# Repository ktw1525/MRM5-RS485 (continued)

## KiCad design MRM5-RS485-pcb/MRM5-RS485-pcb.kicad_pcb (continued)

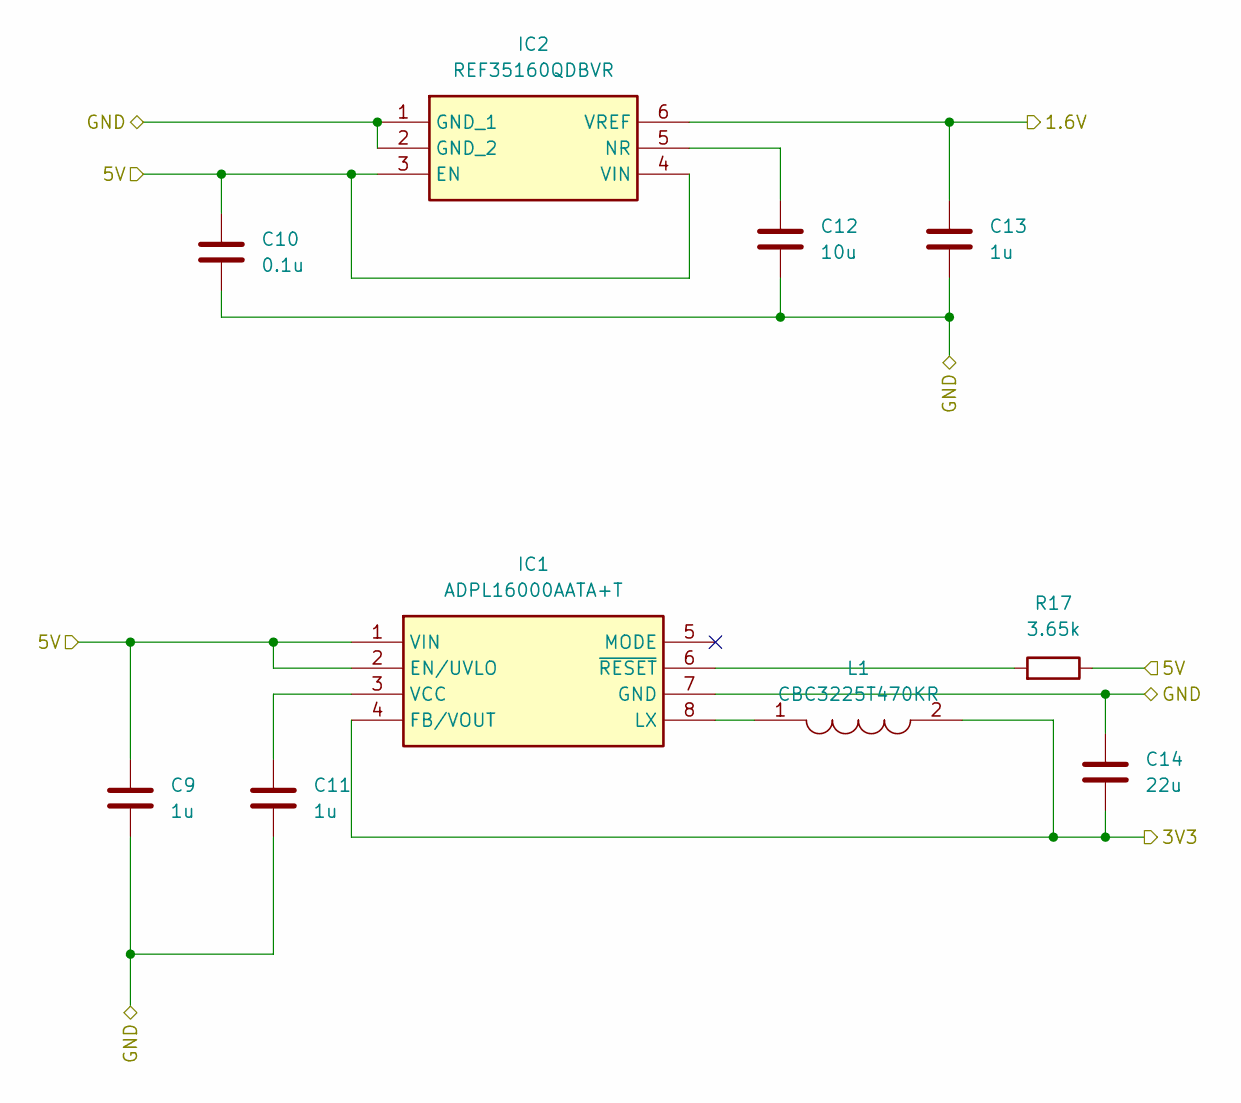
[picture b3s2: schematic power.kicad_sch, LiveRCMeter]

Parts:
C9, C11, C13: 1u; C_0402_1005Metric
C10: 0.1u; C_0402_1005Metric
C12: 10u; C_0805_2012Metric_Pad1.15x1.40mm
C14: 22u; C_0805_2012Metric_Pad1.15x1.40mm
IC1: ADPL16000AATA+T; ADPL16000AATAT; Manufacturer_Part_Number ADPL16000AATA+T; Mouser Part Number 700-ADPL16000AATA+T
IC2: REF35160QDBVR; SOT95P280X145-6N; Manufacturer_Part_Number REF35160QDBVR; Mouser Part Number 595-REF35160QDBVR
L1: CBC3225T470KR; INDC3225X270N; Manufacturer_Part_Number CBC3225T470KR; Mouser Part Number 963-CBC3225T470KR
R17: 3.65k; R_0402_1005Metric

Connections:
+1V6: C13.2, IC2.6 (VREF); also elsewhere on the board
+3V3: C14.1, IC1.4 (FB/VOUT), L1.2; also elsewhere on the board
+5V: C9.2, C10.2, IC1.1 (VIN), IC1.2 (EN/UVLO), IC2.3 (EN), IC2.4 (VIN), R17.2; also elsewhere on the board
GND: C9.1, C10.1, C11.1, C12.1, C13.1, C14.2, IC1.7 (GND), IC2.1 (GND_1), IC2.2 (GND_2); also elsewhere on the board
unnamed: IC1.8 (LX), L1.1
unnamed: C11.2, IC1.3 (VCC)
unnamed: IC1.6 (~RESET), R17.1
unnamed: C12.2, IC2.5 (NR)

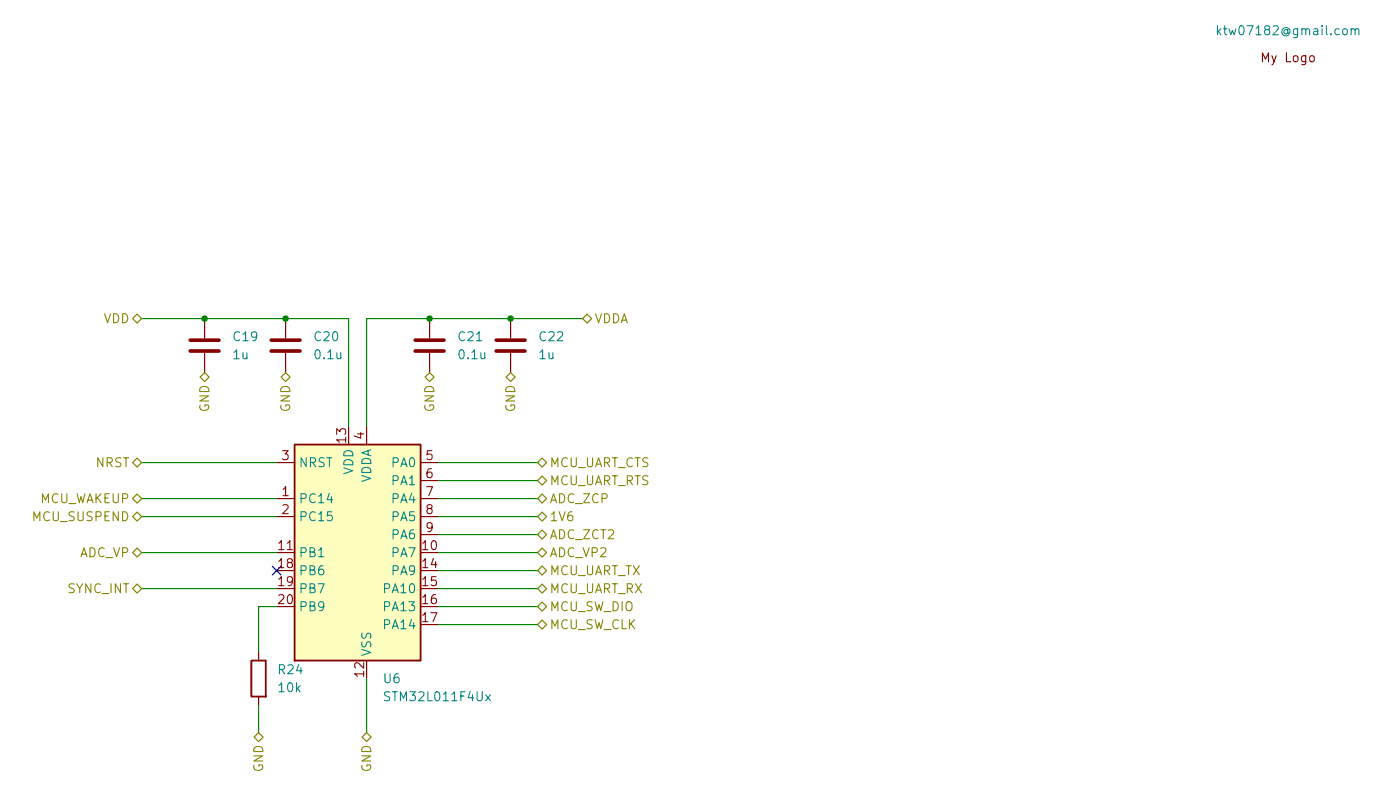
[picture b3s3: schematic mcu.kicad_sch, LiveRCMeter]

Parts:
C19, C22: 1u; C_0402_1005Metric
C20, C21: 0.1u; C_0402_1005Metric
R24: 10k; R_0402_1005Metric
Symbol1: ktw07182@gmail.com; ktw07182_logo
U6: STM32L011F4Ux; ST_UFQFPN-20_3x3mm_P0.5mm

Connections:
+1V6: U6.8 (PA5); also elsewhere on the board
+3V3: C19.2, C20.2, C21.2, C22.2, U6.4 (VDDA), U6.13 (VDD); also elsewhere on the board
/Analog/sigV: U6.11 (PB1); also elsewhere on the board
/Analog/sigV2: U6.10 (PA7); also elsewhere on the board
/Analog/sigZ: U6.7 (PA4); also elsewhere on the board
/Analog/sigZ2: U6.9 (PA6); also elsewhere on the board
/F1: U6.2 (PC15); also elsewhere on the board
/F2: U6.1 (PC14); also elsewhere on the board
/F3: U6.15 (PA10); also elsewhere on the board
/F4: U6.14 (PA9); also elsewhere on the board
/F5: U6.5 (PA0); also elsewhere on the board
/F6: U6.6 (PA1); also elsewhere on the board
/Interface/SYNC: U6.19 (PB7); also elsewhere on the board
/SW1: U6.3 (NRST); also elsewhere on the board
/SW2: U6.17 (PA14); also elsewhere on the board
/SW3: U6.16 (PA13); also elsewhere on the board
GND: C19.1, C20.1, C21.1, C22.1, R24.1, U6.12 (VSS); also elsewhere on the board
unnamed: R24.2, U6.20 (PB9)

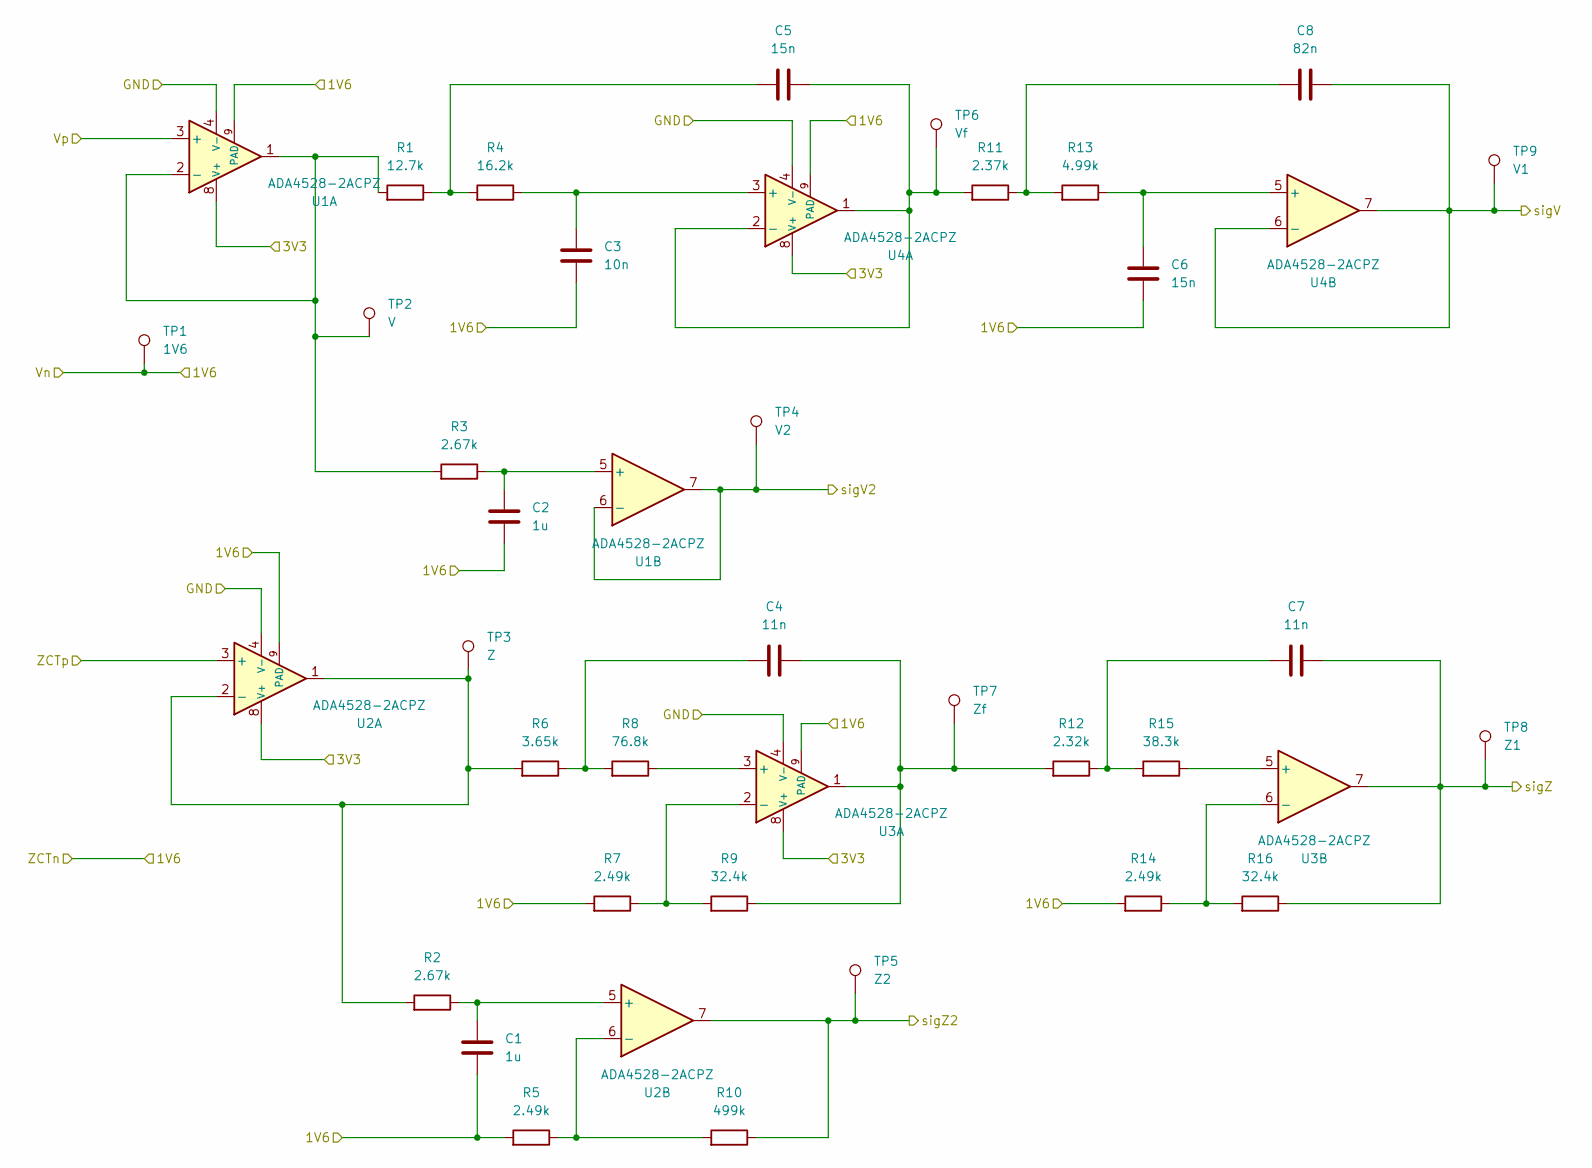
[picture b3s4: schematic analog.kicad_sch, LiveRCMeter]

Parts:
C1, C2: 1u; C_0402_1005Metric
C3: 10n; C_0402_1005Metric
C4, C7: 11n; C_0402_1005Metric
C5, C6: 15n; C_0402_1005Metric
C8: 82n; C_0402_1005Metric
R1: 12.7k; R_0402_1005Metric
R2, R3: 2.67k; R_0402_1005Metric
R4: 16.2k; R_0402_1005Metric
R5, R7, R14: 2.49k; R_0402_1005Metric
R6: 3.65k; R_0402_1005Metric
R8: 76.8k; R_0402_1005Metric
R9, R16: 32.4k; R_0402_1005Metric
R10: 499k; R_0402_1005Metric
R11: 2.37k; R_0402_1005Metric
R12: 2.32k; R_0402_1005Metric
R13: 4.99k; R_0402_1005Metric
R15: 38.3k; R_0402_1005Metric
TP1: 1V6; TestPoint_Pad_D2.0mm
TP2: V; TestPoint_Pad_D2.0mm
TP3: Z; TestPoint_Pad_D2.0mm
TP4: V2; TestPoint_Pad_D2.0mm
TP5: Z2; TestPoint_Pad_D2.0mm
TP6: Vf; TestPoint_Pad_D2.0mm
TP7: Zf; TestPoint_Pad_D2.0mm
TP8: Z1; TestPoint_Pad_D2.0mm
TP9: V1; TestPoint_Pad_D2.0mm
U1, U2, U3, U4: ADA4528-2ACPZ; DFN-8-1EP_3x3mm_P0.5mm_EP1.66x2.38mm

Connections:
+1V6: C1.1, C2.1, C3.1, C6.1, R5.1, R7.1, R14.1, TP1.1, U1.9 (PAD), U2.9 (PAD), U3.9 (PAD), U4.9 (PAD); also elsewhere on the board
+3V3: U1.8 (V+), U2.8 (V+), U3.8 (V+), U4.8 (V+); also elsewhere on the board
/Analog/Vp: U1.3 (+); also elsewhere on the board
/Analog/ZCTp: U2.3 (+); also elsewhere on the board
/Analog/sigV: C8.2, TP9.1, U4.6 (-), U4.7; also elsewhere on the board
/Analog/sigV2: TP4.1, U1.6 (-), U1.7; also elsewhere on the board
/Analog/sigZ: C7.2, R16.2, TP8.1, U3.7; also elsewhere on the board
/Analog/sigZ2: R10.2, TP5.1, U2.7; also elsewhere on the board
GND: U1.4 (V-), U2.4 (V-), U3.4 (V-), U4.4 (V-); also elsewhere on the board
unnamed: C4.1, R6.2, R8.1
unnamed: C4.2, R9.2, R12.1, TP7.1, U3.1
unnamed: C5.1, R1.2, R4.1
unnamed: C7.1, R12.2, R15.1
unnamed: C8.1, R11.2, R13.1
unnamed: R1.1, R3.1, TP2.1, U1.1, U1.2 (-)
unnamed: C2.2, R3.2, U1.5 (+)
unnamed: R2.1, R6.1, TP3.1, U2.1, U2.2 (-)
unnamed: C1.2, R2.2, U2.5 (+)
unnamed: R5.2, R10.1, U2.6 (-)
unnamed: R8.2, U3.3 (+)
unnamed: R7.2, R9.1, U3.2 (-)
unnamed: R15.2, U3.5 (+)
unnamed: R14.2, R16.1, U3.6 (-)
unnamed: C3.2, R4.2, U4.3 (+)
unnamed: C5.2, R11.1, TP6.1, U4.1, U4.2 (-)
unnamed: C6.2, R13.2, U4.5 (+)

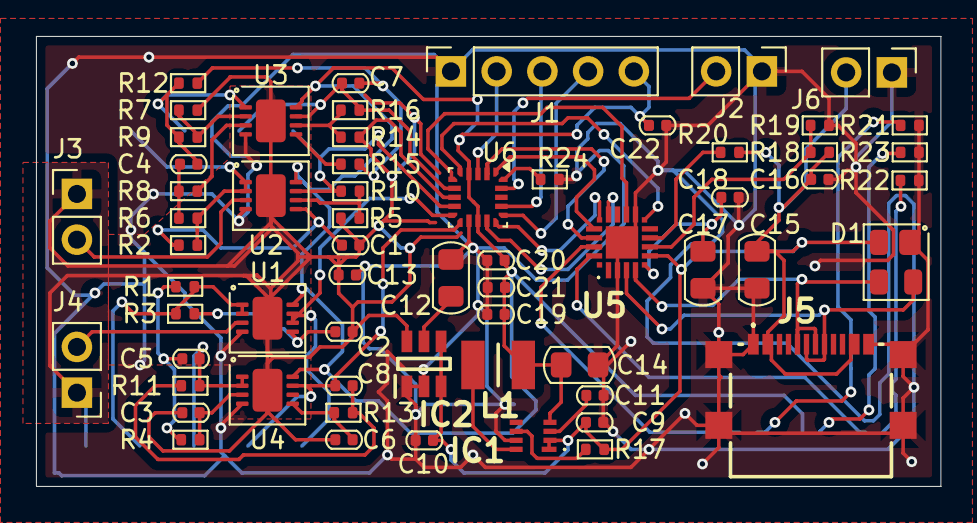
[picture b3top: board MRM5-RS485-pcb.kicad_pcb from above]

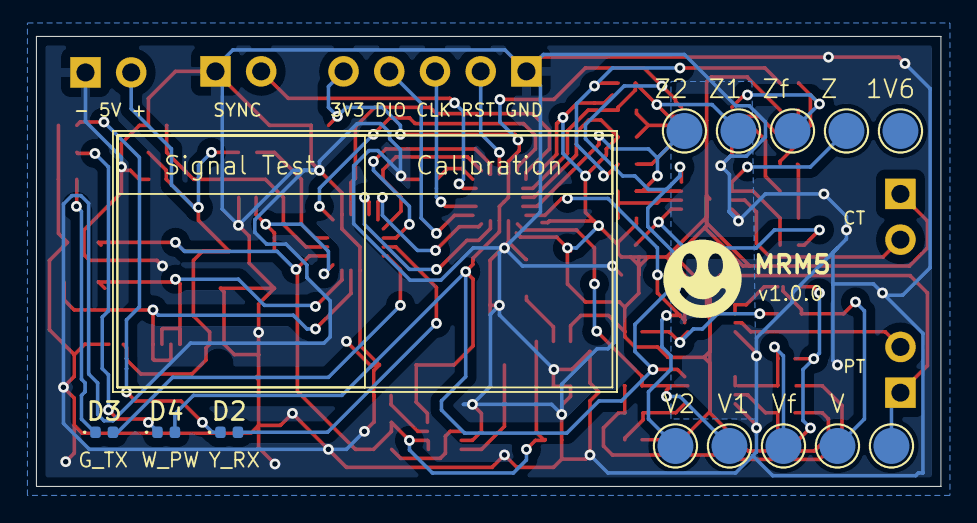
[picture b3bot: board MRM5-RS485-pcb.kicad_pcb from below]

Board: 2 copper layers, 50.2 x 25.0 mm, 76 parts (14 on the bottom side), 52 nets.

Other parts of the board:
TP1#2: 1V6; TestPoint_Pad_D2.0mm

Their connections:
+1V6: TP1#2.1; also elsewhere on the board

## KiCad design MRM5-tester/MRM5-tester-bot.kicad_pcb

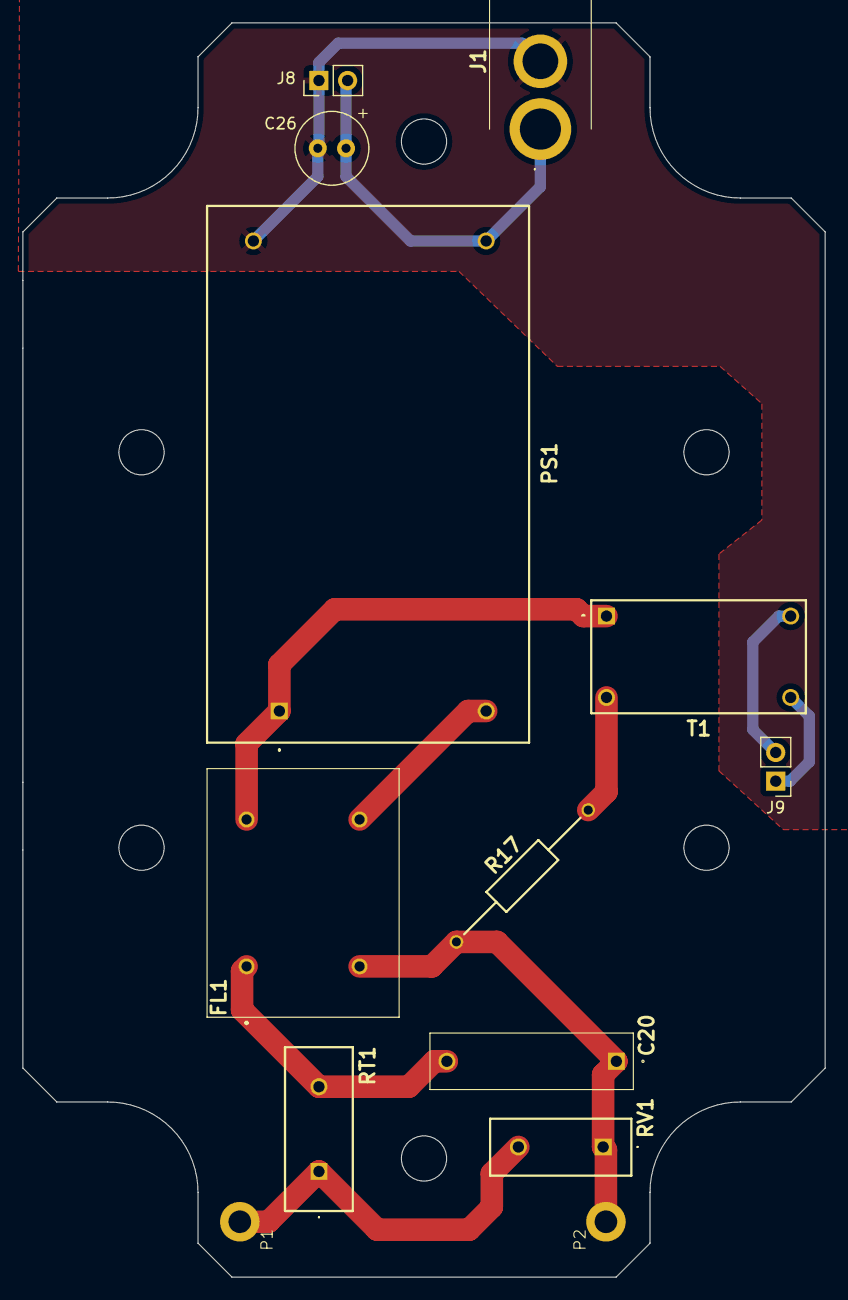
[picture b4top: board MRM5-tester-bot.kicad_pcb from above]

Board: 2 copper layers, 71.0 x 111.0 mm, 13 parts (0 on the bottom side), 10 nets.

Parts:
C20: X2-15B( 0.1uF / 275V); B32922X__18_X_5_
C26: 220uF 16V 105℃; C_Radial_D6.3mm_H11.0mm_P2.50mm
FL1: SS21V-R110100; SSHB10HSR11100
J1: PJ-037AH; PJ037AH
J8, J9: Conn_01x02; PinHeader_1x02_P2.54mm_Vertical
P1, P2: PAD_Hole_D2mm
PS1: HLK-15M05C; HLK15M05C
R17: 1MΩ 1W; RESAD1650W60L650D250
RT1: NTC10D-11; NTC10D11
RV1: MOV-10D391K; MOV10D391K
T1: ZMPT107-1; ZMPT1071

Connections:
/analog/PT1_bot: J9.1, T1.4
/analog/PT2_bot: J9.2, T1.3
/analog/Vn_h: C20.1, FL1.2, P2.1, R17.1, RV1.1
/analog/Vp_ssh: R17.2, T1.2
/interface/5V_bot: C26.1, J1.1, J8.2, PS1.4 (+V0)
/interface/GND_bot: C26.2, J1.2, J8.1, PS1.3 (-V0)
/interface/Vp_h: P1.1, RT1.1, RV1.2
/power/FL1_in1_sh: C20.2, FL1.1, RT1.2
/power/FL1_out1_sh: FL1.4, PS1.1 (AC_1), T1.1
/power/FL1_out2_sh: FL1.3, PS1.2 (AC_2)

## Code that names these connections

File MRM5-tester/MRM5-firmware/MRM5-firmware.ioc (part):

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Mcu.Name=STM32G051F(6-8)Px
Mcu.Package=TSSOP20
Mcu.UserName=STM32G051F8Px
PA0.GPIOParameters=GPIO_Label
PA0.GPIO_Label=ADC_V
PA0.Mode=IN0
PA0.Signal=ADC1_IN0
PA1.GPIOParameters=GPIO_Label
PA1.GPIO_Label=ADC_1V6
PA1.Mode=IN1
PA1.Signal=ADC1_IN1
PA13.Mode=Serial_Wire
PA13.Signal=SYS_SWDIO
PA14-BOOT0.Mode=Serial_Wire
PA14-BOOT0.Signal=SYS_SWCLK
PA14-BOOT0__PA15.StandardMode=true
PA2.GPIOParameters=GPIO_Label
PA2.GPIO_Label=ADC_Zf
PA2.Mode=IN2
PA2.Signal=ADC1_IN2
PA3.GPIOParameters=GPIO_Label
PA3.GPIO_Label=SYNC_INT
PA3.Signal=GPXTI3
PA4.GPIOParameters=GPIO_Label
PA4.GPIO_Label=DAC_Z
PA4.Signal=COMP_DAC11_group
PA5.GPIOParameters=GPIO_Label
PA5.GPIO_Label=IFLAG_Z
PA5.Signal=GPXTI5
PA6.GPIOParameters=GPIO_Label
PA6.GPIO_Label=TFLAG_Z
PA6.Signal=GPXTI6
PA7.GPIOParameters=GPIO_Label
PA7.GPIO_Label=IFLAG_1V6
PA7.Signal=GPXTI7
PB0.GPIOParameters=GPIO_Label
PB0.GPIO_Label=TFLAG_1V6
PB0.Signal=GPXTI0
PB0__PB1__PB2__PA8.StandardMode=true
PB3__PB4__PB5__PB6.StandardMode=true
PB6.Mode=Asynchronous
PB6.Signal=USART1_TX
PB7.Mode=Asynchronous
PB7.Signal=USART1_RX
PB7__PB8.StandardMode=true
PC14-OSC32_IN\ (PC14).Signal=GPXTI14
PC14-OSC32_IN\ (PC14)__PB9.StandardMode=true
PF2-NRST.GPIOParameters=GPIO_Label
PF2-NRST.GPIO_Label=MCU_NRST
PF2-NRST.Signal=GPXTI2
RCC.HSE_VALUE=8000000
RCC.SYSCLKFreq_VALUE=64000000
RCC.SYSCLKSource=RCC_SYSCLKSOURCE_PLLCLK
board=custom

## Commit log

2024-11-30 logo added on pcb
2024-12-01 sensor is added
2024-12-02 MRM5-tester added
2024-12-03 tester updated
2024-12-03 tester updated 회로도 제작중
2024-12-04 tester PCB 작성중
2024-12-05 tester pcb 디자인 완료
2024-12-05 tester PCB 검토
2024-12-09 MRM5-tester updated
2024-12-09 case design 시작
2024-12-09 case updated
2024-12-10 tester pcb updated
2024-12-10 pcb updated
2024-12-10 case found!
2024-12-11 전류 입력시의 경우를 고려한 회로 추가
2024-12-11 케이스에 마춰서 제작 중
2024-12-13 1차 마감
2024-12-13 PCB 제작 1차 마감
2024-12-17 MRM5-tester-updated
2024-12-19 MRM5-Sensor updated
2024-12-26 case fixed
2025-01-03 firmware updated
2025-01-06 offset added
2025-01-22 fixed
2025-02-11 불필요한 것 제거
